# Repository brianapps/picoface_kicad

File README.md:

# picoFace KiCad

The picoFace is an inexpensive device for the Sinclair ZX Spectrum that use a Raspberry Pi Pico to provide a Multiface style support. 

See the main picoFace repository for more info https://github.com/brianapps/picoface_poc.

## Info

The circuit board is relatively simple.

The two ATF16V8B chips are programmed with logic provided in the [main picoFace repo](https://github.com/brianapps/picoface_poc).

The design uses a number of custom symbols:
* A modified RPi Pico part without the debug pins on the footprint.
* A custom part for the SD module to match a very cheap and generic one from AliExpress.
* Symbols for the two PLDs. These are updated automatically using a Python script from the [main repo](https://github.com/brianapps/picoface_poc).

## License

picoFace is free software: you can redistribute it and/or modify it under the terms of
the GNU General Public License as published by the Free Software Foundation, either
version 3 of the License, or (at your option) any later version.

picoFace is distributed in the hope that it will be useful, but WITHOUT ANY WARRANTY; 
without even the implied warranty of MERCHANTABILITY or FITNESS FOR A PARTICULAR PURPOSE.
See the GNU General Public License for more details.

A copy of the license is provided in the [LICENSE](./LICENSE) file.

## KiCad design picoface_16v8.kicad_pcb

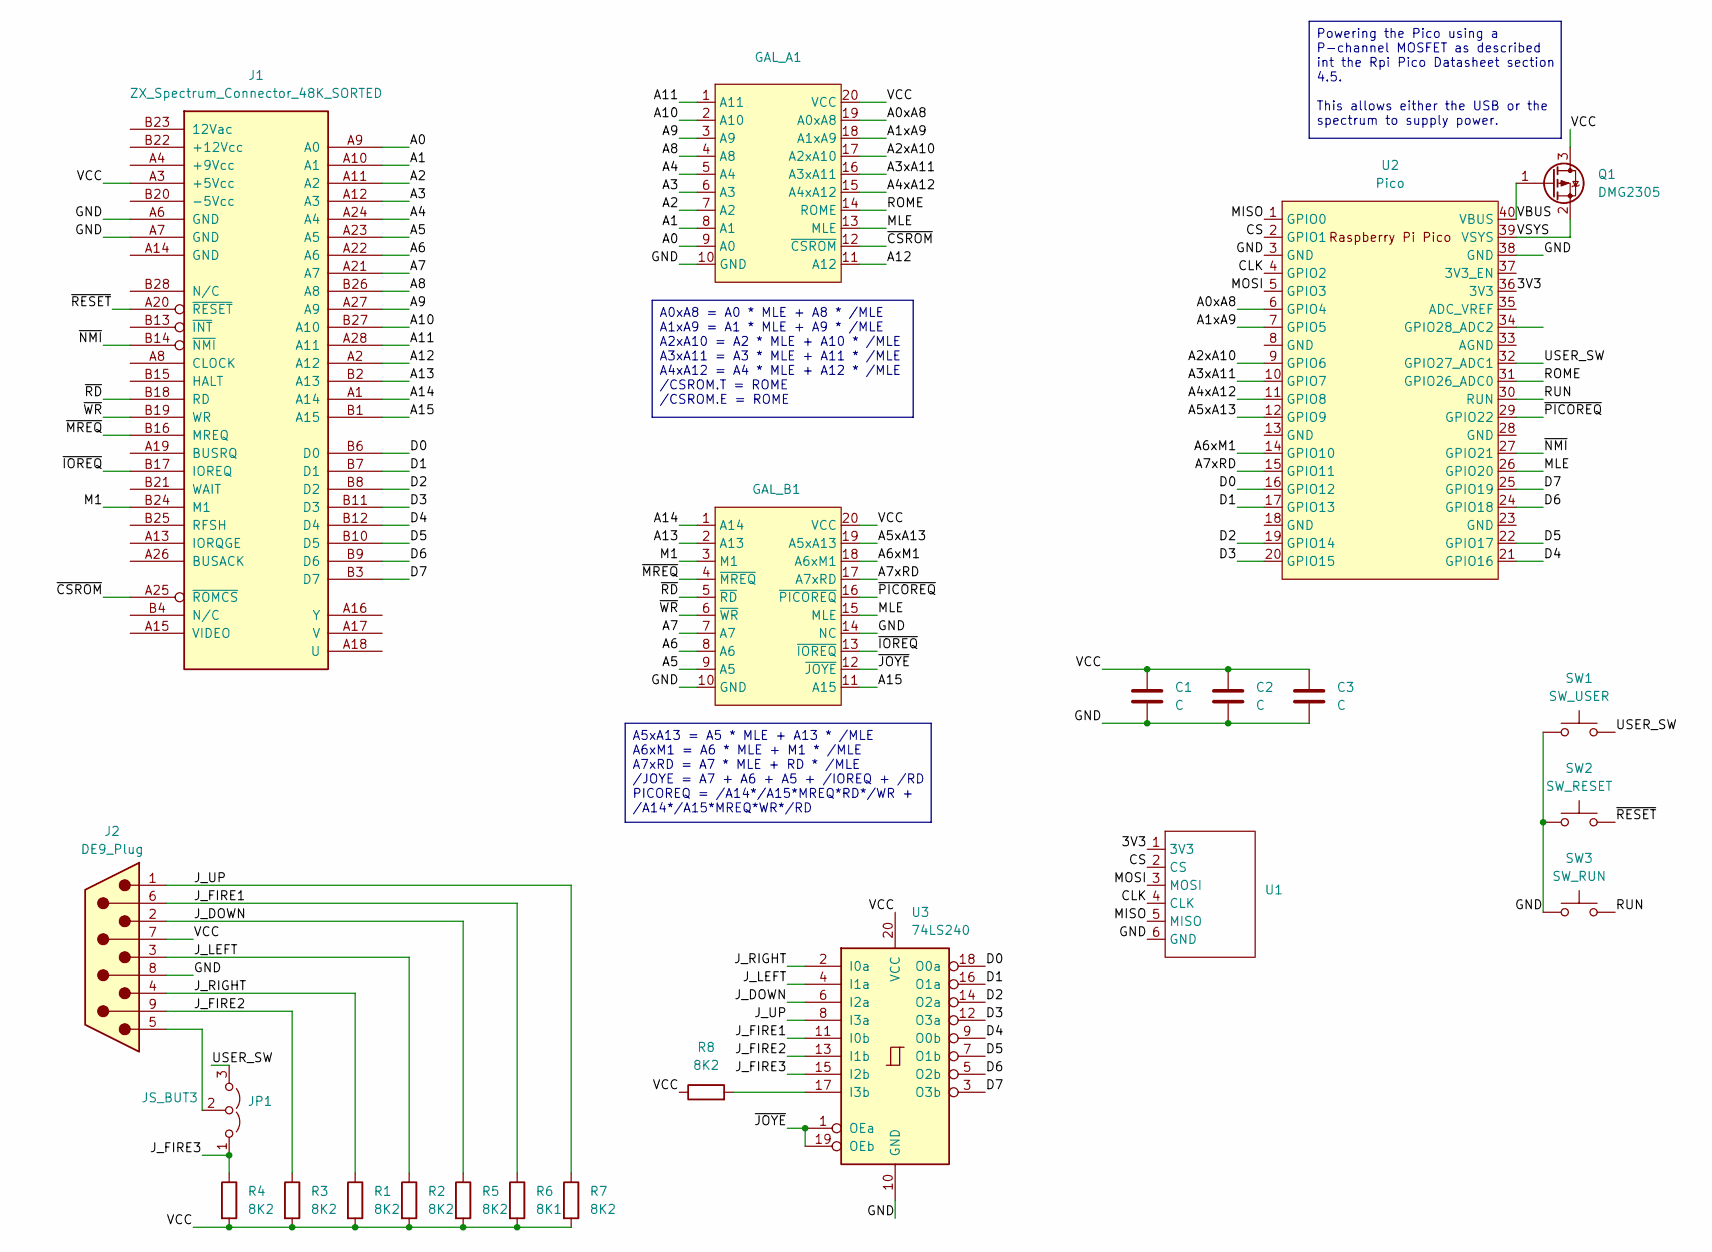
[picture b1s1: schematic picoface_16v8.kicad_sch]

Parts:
C1, C2, C3: C; C_Disc_D5.0mm_W2.5mm_P2.50mm
GAL_A1: DIP-20_W7.62mm_Socket
GAL_B1: DIP-20_W7.62mm_Socket
J1: ZX_Spectrum_Connector_48K_SORTED; ZX_CONN
J2: DE9_Plug; DSUB-9_Female_Vertical_P2.77x2.84mm_MountingHoles
JP1: JS_BUT3; PinHeader_1x03_P2.54mm_Vertical
Q1: DMG2305; SOT-23
R1, R2, R3, R4, R5, R7, R8: 8K2; R_Axial_DIN0204_L3.6mm_D1.6mm_P7.62mm_Horizontal
R6: 8K1; R_Axial_DIN0204_L3.6mm_D1.6mm_P7.62mm_Horizontal
SW1: SW_USER; SW_PUSH_6mm_H8mm
SW2: SW_RESET; SW_PUSH_6mm_H8mm
SW3: SW_RUN; SW_PUSH_6mm_H8mm
U1: SDMICRO_ALIEXPRESS
U2: Pico; RPi_Pico_SMD_TH_BA
U3: 74LS240; DIP-20_W7.62mm_Socket

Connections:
/3V3: U1.1 (3V3), U2.36 (3V3)
/A0: GAL_A1.9 (A0), J1.A9 (A0)
/A0xA8: GAL_A1.19 (A0xA8), U2.6 (GPIO4)
/A1: GAL_A1.8 (A1), J1.A10 (A1)
/A1xA9: GAL_A1.18 (A1xA9), U2.7 (GPIO5)
/A2: GAL_A1.7 (A2), J1.A11 (A2)
/A2xA10: GAL_A1.17 (A2xA10), U2.9 (GPIO6)
/A3: GAL_A1.6 (A3), J1.A12 (A3)
/A3xA11: GAL_A1.16 (A3xA11), U2.10 (GPIO7)
/A4: GAL_A1.5 (A4), J1.A24 (A4)
/A4xA12: GAL_A1.15 (A4xA12), U2.11 (GPIO8)
/A5: GAL_B1.9 (A5), J1.A23 (A5)
/A5xA13: GAL_B1.19 (A5xA13), U2.12 (GPIO9)
/A6: GAL_B1.8 (A6), J1.A22 (A6)
/A6xM1: GAL_B1.18 (A6xM1), U2.14 (GPIO10)
/A7: GAL_B1.7 (A7), J1.A21 (A7)
/A7xRD: GAL_B1.17 (A7xRD), U2.15 (GPIO11)
/A8: GAL_A1.4 (A8), J1.B26 (A8)
/A9: GAL_A1.3 (A9), J1.A27 (A9)
/A10: GAL_A1.2 (A10), J1.B27 (A10)
/A11: GAL_A1.1 (A11), J1.A28 (A11)
/A12: GAL_A1.11 (A12), J1.A2 (A12)
/A13: GAL_B1.2 (A13), J1.B2 (A13)
/A14: GAL_B1.1 (A14), J1.A1 (A14)
/A15: GAL_B1.11 (A15), J1.B1 (A15)
/CLK: U1.4 (CLK), U2.4 (GPIO2)
/CS: U1.2 (CS), U2.2 (GPIO1)
/D0: J1.B6 (D0), U2.16 (GPIO12), U3.18 (O0a)
/D1: J1.B7 (D1), U2.17 (GPIO13), U3.16 (O1a)
/D2: J1.B8 (D2), U2.19 (GPIO14), U3.14 (O2a)
/D3: J1.B11 (D3), U2.20 (GPIO15), U3.12 (O3a)
/D4: J1.B12 (D4), U2.21 (GPIO16), U3.9 (O0b)
/D5: J1.B10 (D5), U2.22 (GPIO17), U3.7 (O1b)
/D6: J1.B9 (D6), U2.24 (GPIO18), U3.5 (O2b)
/D7: J1.B3 (D7), U2.25 (GPIO19), U3.3 (O3b)
/GND: C1.2, C2.2, C3.2, GAL_A1.10 (GND), GAL_B1.10 (GND), GAL_B1.14 (NC), J1.A6 (GND), J1.A7 (GND), J2.8, SW1.1, SW2.1, SW3.1, U1.6 (GND), U2.3 (GND), U2.38 (GND), U3.10 (GND)
/J_DOWN: J2.2, R5.1, U3.6 (I2a)
/J_FIRE1: J2.6, R6.1, U3.11 (I0b)
/J_FIRE2: J2.9, R3.1, U3.13 (I1b)
/J_FIRE3: JP1.1 (A), R4.1, U3.15 (I2b)
/J_LEFT: J2.3, R2.1, U3.4 (I1a)
/J_RIGHT: J2.4, R1.1, U3.2 (I0a)
/J_UP: J2.1, R7.1, U3.8 (I3a)
/M1: GAL_B1.3 (M1), J1.B24 (M1)
/MISO: U1.5 (MISO), U2.1 (GPIO0)
/MLE: GAL_A1.13 (MLE), GAL_B1.15 (MLE), U2.26 (GPIO20)
/MOSI: U1.3 (MOSI), U2.5 (GPIO3)
/ROME: GAL_A1.14 (ROME), U2.31 (GPIO26_ADC0)
/RUN: SW3.2, U2.30 (RUN)
/USER_SW: JP1.3 (B), SW1.2, U2.32 (GPIO27_ADC1)
/VBUS: Q1.1 (G), U2.40 (VBUS)
/VCC: C1.1, C2.1, C3.1, GAL_A1.20 (VCC), GAL_B1.20 (VCC), J1.A3 (+5Vcc), J2.7, Q1.3 (D), R1.2, R2.2, R3.2, R4.2, R5.2, R6.2, R7.2, R8.1, U3.20 (VCC)
/VSYS: Q1.2 (S), U2.39 (VSYS)
/~CSROM: GAL_A1.12 (~CSROM), J1.A25 (~ROMCS)
/~IOREQ: GAL_B1.13 (~IOREQ), J1.B17 (IOREQ)
/~JOYE: GAL_B1.12 (~JOYE), U3.1 (OEa), U3.19 (OEb)
/~MREQ: GAL_B1.4 (~MREQ), J1.B16 (MREQ)
/~NMI: J1.B14 (~NMI), U2.27 (GPIO21)
/~PICOREQ: GAL_B1.16 (~PICOREQ), U2.29 (GPIO22)
/~RD: GAL_B1.5 (~RD), J1.B18 (RD)
/~RESET: J1.A20 (~RESET), SW2.2
/~WR: GAL_B1.6 (~WR), J1.B19 (WR)
unnamed: J2.5, JP1.2 (C)
unnamed: R8.2, U3.17 (I3b)

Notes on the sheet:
Powering the Pico using a P-channel MOSFET as described int the Rpi Pico Datasheet section 4.5. This allows either the USB or the spectrum to supply power.
A0xA8 = A0 * MLE + A8 * /MLE A1xA9 = A1 * MLE + A9 * /MLE A2xA10 = A2 * MLE + A10 * /MLE A3xA11 = A3 * MLE + A11 * /MLE A4xA12 = A4 * MLE + A12 * /MLE /CSROM.T = ROME /CSROM.E = ROME
A5xA13 = A5 * MLE + A13 * /MLE A6xM1 = A6 * MLE + M1 * /MLE A7xRD = A7 * MLE + RD * /MLE /JOYE = A7 + A6 + A5 + /IOREQ + /RD PICOREQ = /A14*/A15*MREQ*RD*/WR + /A14*/A15*MREQ*WR*/RD

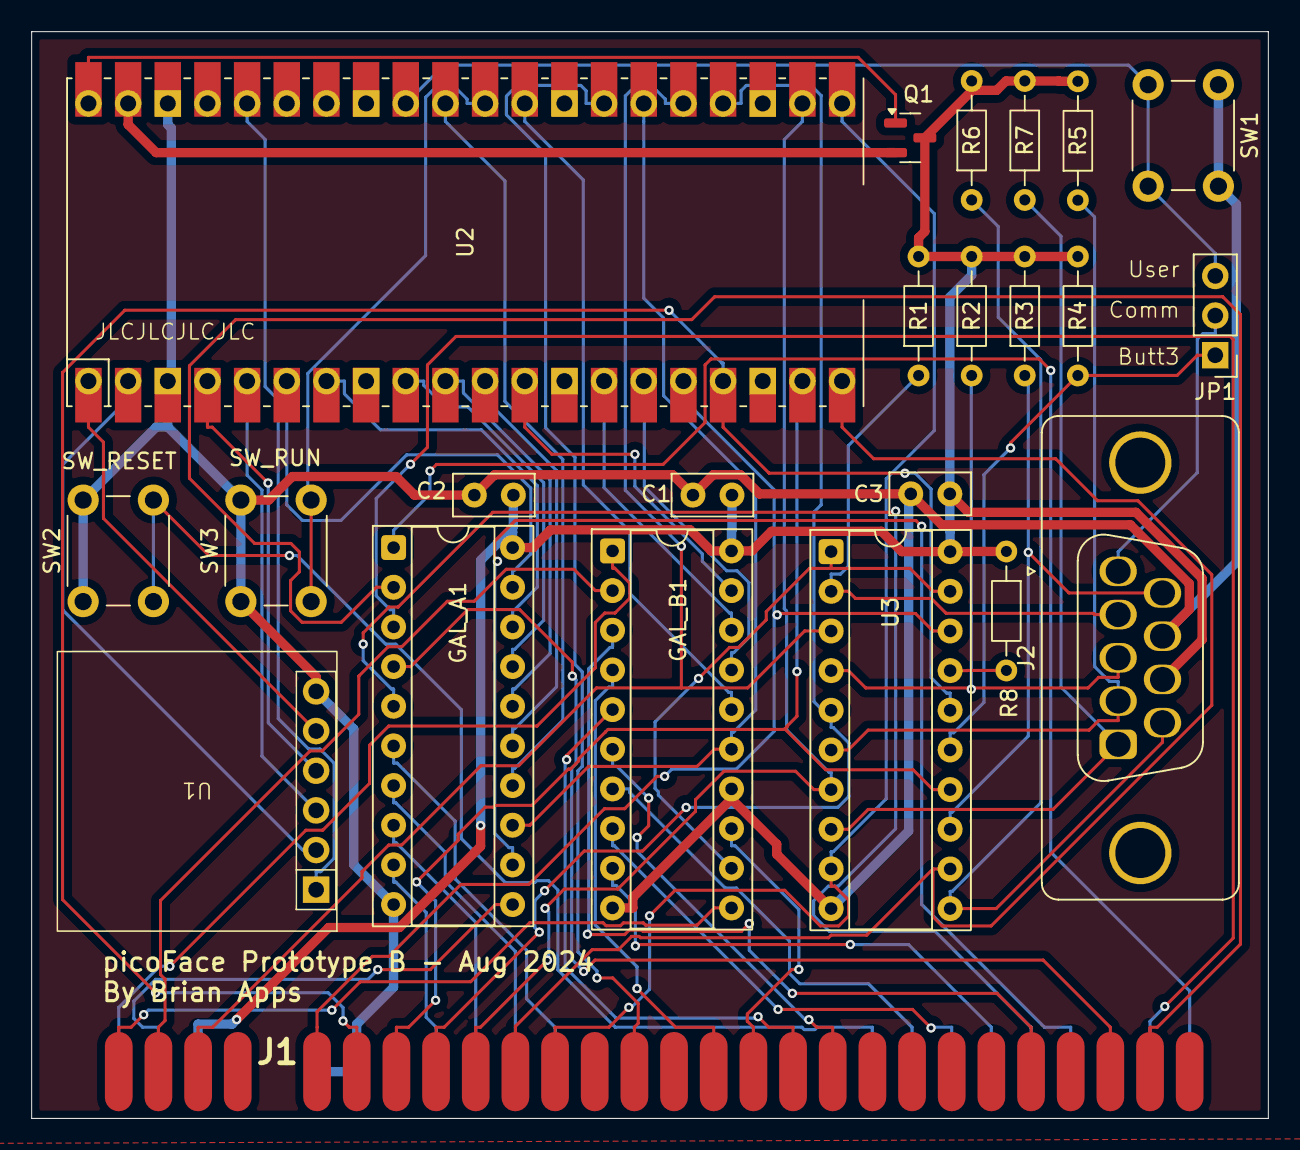
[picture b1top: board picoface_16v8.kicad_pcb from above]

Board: 2 copper layers, 79.2 x 69.6 mm, 23 parts (0 on the bottom side), 64 nets.

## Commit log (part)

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2024-07-24 First prototype picoFace board
2024-07-25 Picoface prototype a board
    This includes the gerbers as sent to JCL PCB for the initial
    prototype board.
2024-08-07 Prototype B board, fix up mistakes in prototype A
    Correct the joystick up connection, make SD card drill holes slightly larger.
2024-08-30 Prototype B with pico ultimate pinout
    Has two set of pads for the different types of pico.
2024-09-02 Correct resistor typo and add GALASM to schematic
    I just blindly typed in 8K1 whereas the resistor I have are 8K2.
2024-09-12 Add updated schematic PDF
2024-09-12 Add readme and license
